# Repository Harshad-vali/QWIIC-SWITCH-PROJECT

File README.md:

# Modular I2C GPIO Expander / Power Switch Board (Qwiic-Compatible)

A compact, Qwiic-compatible power switch module built around an I2C GPIO expander, designed for easy integration into modular sensor/electronics setups without extra wiring or a microcontroller doing the switching directly.

## Overview

This board lets a host microcontroller switch power to a downstream load over I2C, using a GPIO expander instead of dedicated GPIO pins. It's designed to snap into the Qwiic ecosystem, so it can be daisy-chained with other Qwiic boards with no soldering.

## Key Features

- **I2C-controlled power switching** using the PCA9536 GPIO expander
- **PCA9306 I2C level shifter** for safe voltage-level translation between 3.3V and 5V I2C buses
- **Impedance-controlled I2C routing** to keep signal integrity clean on the bus
- **MOSFET switching circuitry** for the actual load power path
- **Status LED indicators** showing real-time switch state at a glance
- **Qwiic-compatible connectors** for plug-and-play integration with other boards

## Design Details

- Schematic capture and PCB layout done fully in KiCad
- Routed with attention to I2C trace impedance to avoid signal integrity issues on the bus
- Component placement optimized for a compact footprint
- Manufacturing-ready output: complete BOM, Gerber files, and drill files generated for fabrication

### Copper Layers

### Assembly Layers

### Schematic

Full schematic PDF: [Qwiic_Power_Switch_Schematic_v10.pdf](Qwiic_Power_Switch_Schematic_v10%20(1).pdf)

## Tools Used

- KiCad (schematic capture + PCB layout)

## Files in This Repo

- `power switch.kicad_sch` / `power switch.kicad_pcb` / `power switch.kicad_pro` — full KiCad project
- `Qwiic_Power_Switch_Schematic_v10 (1).pdf` — full schematic
- `3D front layer.png`, `3D back layer.png`, `3D side view.png` — 3D renders
- `front cu layer.png`, `back cu layer.png`, `all cu layers.png` — copper layer views
- `front assemble layer.png`, `back assemble layer.png` — assembly drawings
- `schematic.png` — schematic preview image
- `power switch proj 3 main bom.xlsx` — bill of materials with supplier part numbers

## What I'd Improve Next

- Add reverse-polarity protection on the input
- Explore a smaller PCA9536 package option to shrink the footprint further

---
*Part of a PCB design training program (SUREPROED). Designed and routed independently as part of the coursework.*

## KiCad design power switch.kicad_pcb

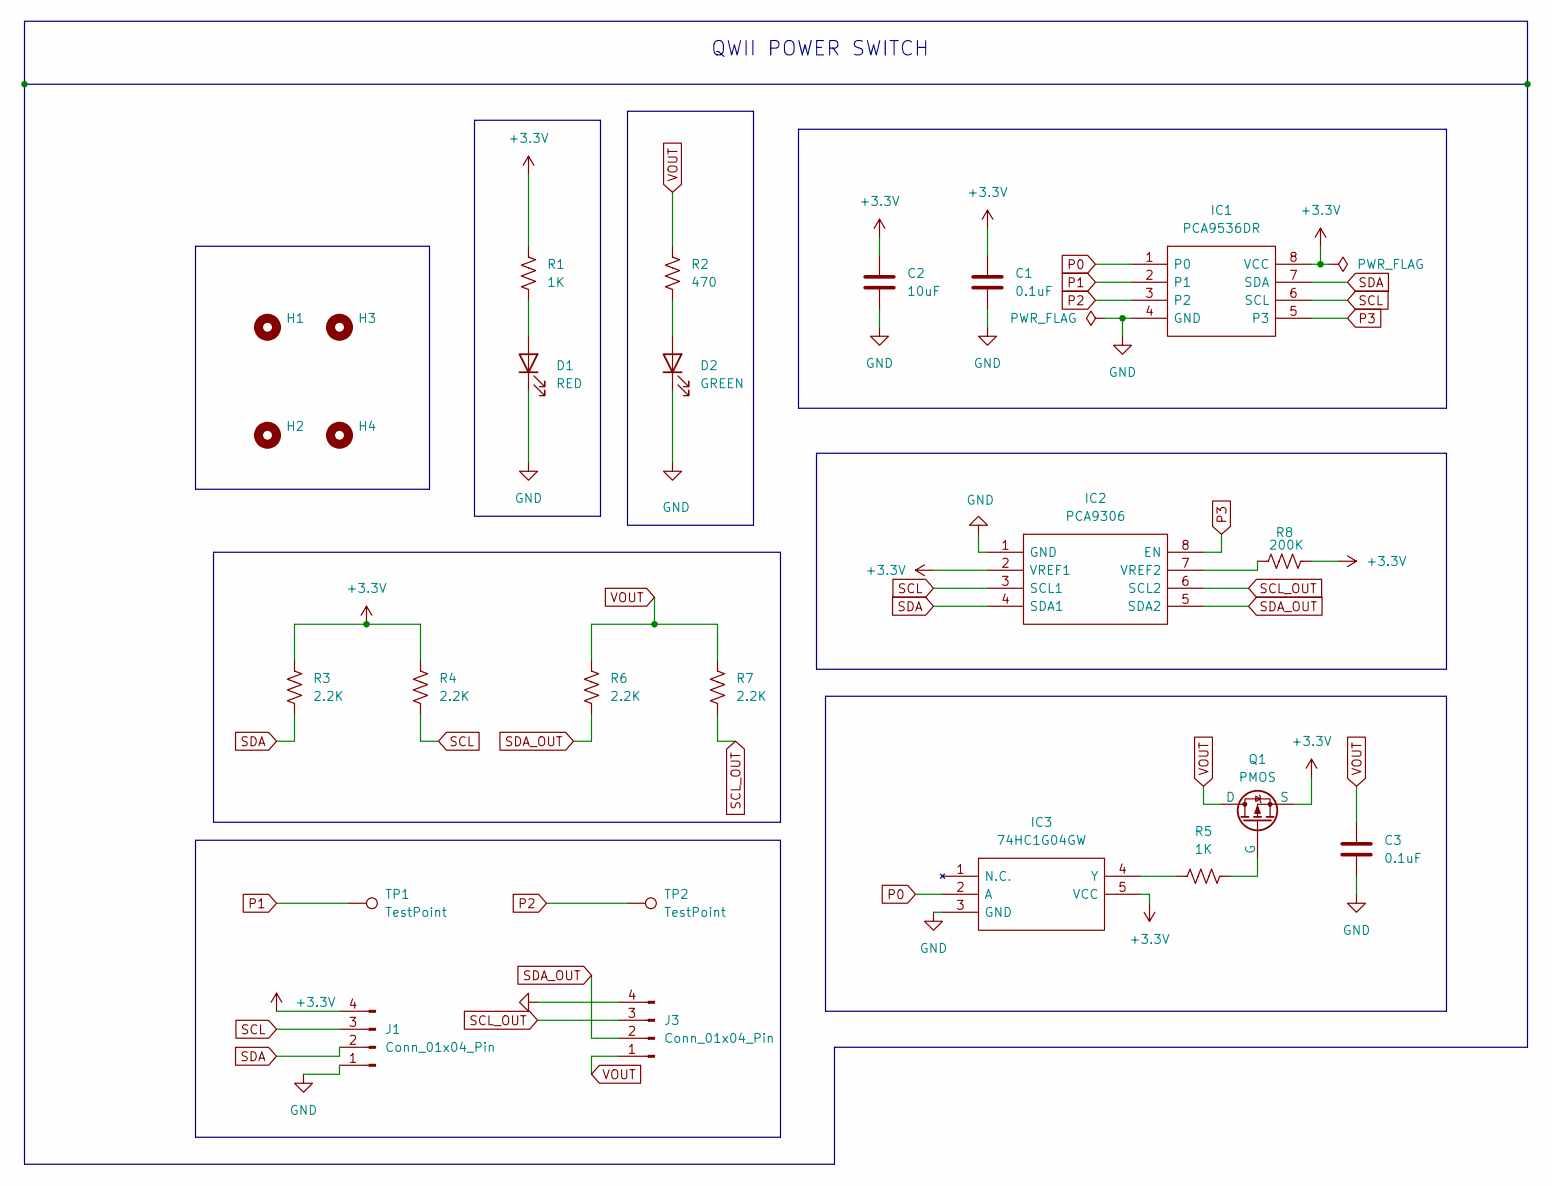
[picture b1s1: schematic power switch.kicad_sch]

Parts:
C1, C3: 0.1uF; C_0805_2012Metric; Manufacturer_Part_Number CC0805KPX7R9BB104
C2: 10uF; C_0603_1608Metric; Manufacturer_Part_Number C0603C106M9PAC7411
D1: RED; LED_0805_2012Metric; Manufacturer_Part_Number 150080RS75000
D2: GREEN; LED_0805_2012Metric; Manufacturer_Part_Number 150080GS75000
H1, H2, H3, H4: MountingHole; MountingHole_2.1mm
IC1: PCA9536DR; PCA9536; Manufacturer_Part_Number PCA9536DR
IC2: PCA9306; Manufacturer_Part_Number PCA9306
IC3: 74HC1G04GW; U1G1 NEW; Manufacturer_Part_Number 74HC1G04GW,125
J1, J3: Conn_01x04_Pin; PinHeader_1x04_P2.54mm_Vertical; Manufacturer_Part_Number D01-9922046
Q1: PMOS; SOT-23; Manufacturer_Part_Number PJS6631_S2_00001
R1, R5: 1K; R_0805_2012Metric; Manufacturer_Part_Number RC0805FR-071KL
R2: 470; R_0805_2012Metric; Manufacturer_Part_Number RC0805FR-07470RL
R3, R4, R6, R7: 2.2K; R_0805_2012Metric; Manufacturer_Part_Number RC0805FR-072K2L
R8: 200K; R_0805_2012Metric; Manufacturer_Part_Number RC0805FR-07200KL
TP1, TP2: TestPoint; TestPoint_Pad_D1.0mm

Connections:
+3.3V: C1.1, C2.1, IC1.8 (VCC), IC2.2 (VREF1), IC3.5 (VCC), J1.4, Q1.3 (S), R1.1, R3.1, R4.1, R8.2
GND: C1.2, C2.2, C3.2, D1.1 (K), D2.1 (K), IC1.4 (GND), IC2.1 (GND), IC3.3 (GND), J1.1, J3.4
unnamed: D1.2 (A), R1.2
unnamed: D2.2 (A), R2.2
unnamed: IC2.7 (VREF2), R8.1
unnamed: IC3.4 (Y), R5.1
unnamed: Q1.2 (G), R5.2
P0: IC1.1 (P0), IC3.2 (A)
P1: IC1.2 (P1), TP1.1
P2: IC1.3 (P2), TP2.1
P3: IC1.5 (P3), IC2.8 (EN)
SCL: IC1.6 (SCL), IC2.3 (SCL1), J1.3, R4.2
SCL_OUT: IC2.6 (SCL2), J3.3, R7.2
SDA: IC1.7 (SDA), IC2.4 (SDA1), J1.2, R3.2
SDA_OUT: IC2.5 (SDA2), J3.2, R6.2
VOUT: C3.1, J3.1, Q1.1 (D), R2.1, R6.1, R7.1

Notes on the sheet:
QWII POWER SWITCH

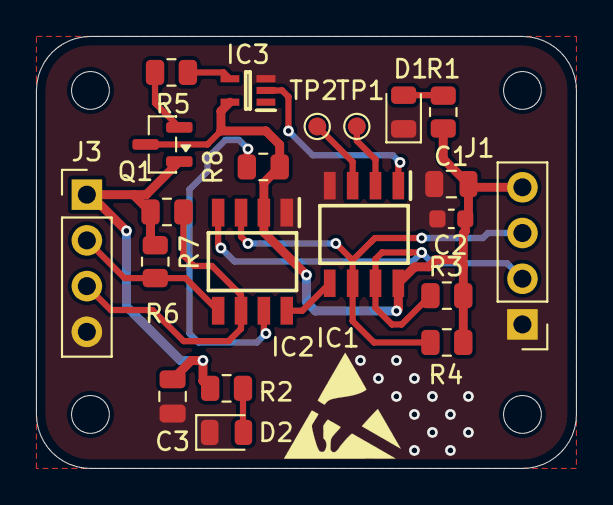
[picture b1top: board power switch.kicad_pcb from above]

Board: 2 copper layers, 30.0 x 24.0 mm, 25 parts (0 on the bottom side), 16 nets.
